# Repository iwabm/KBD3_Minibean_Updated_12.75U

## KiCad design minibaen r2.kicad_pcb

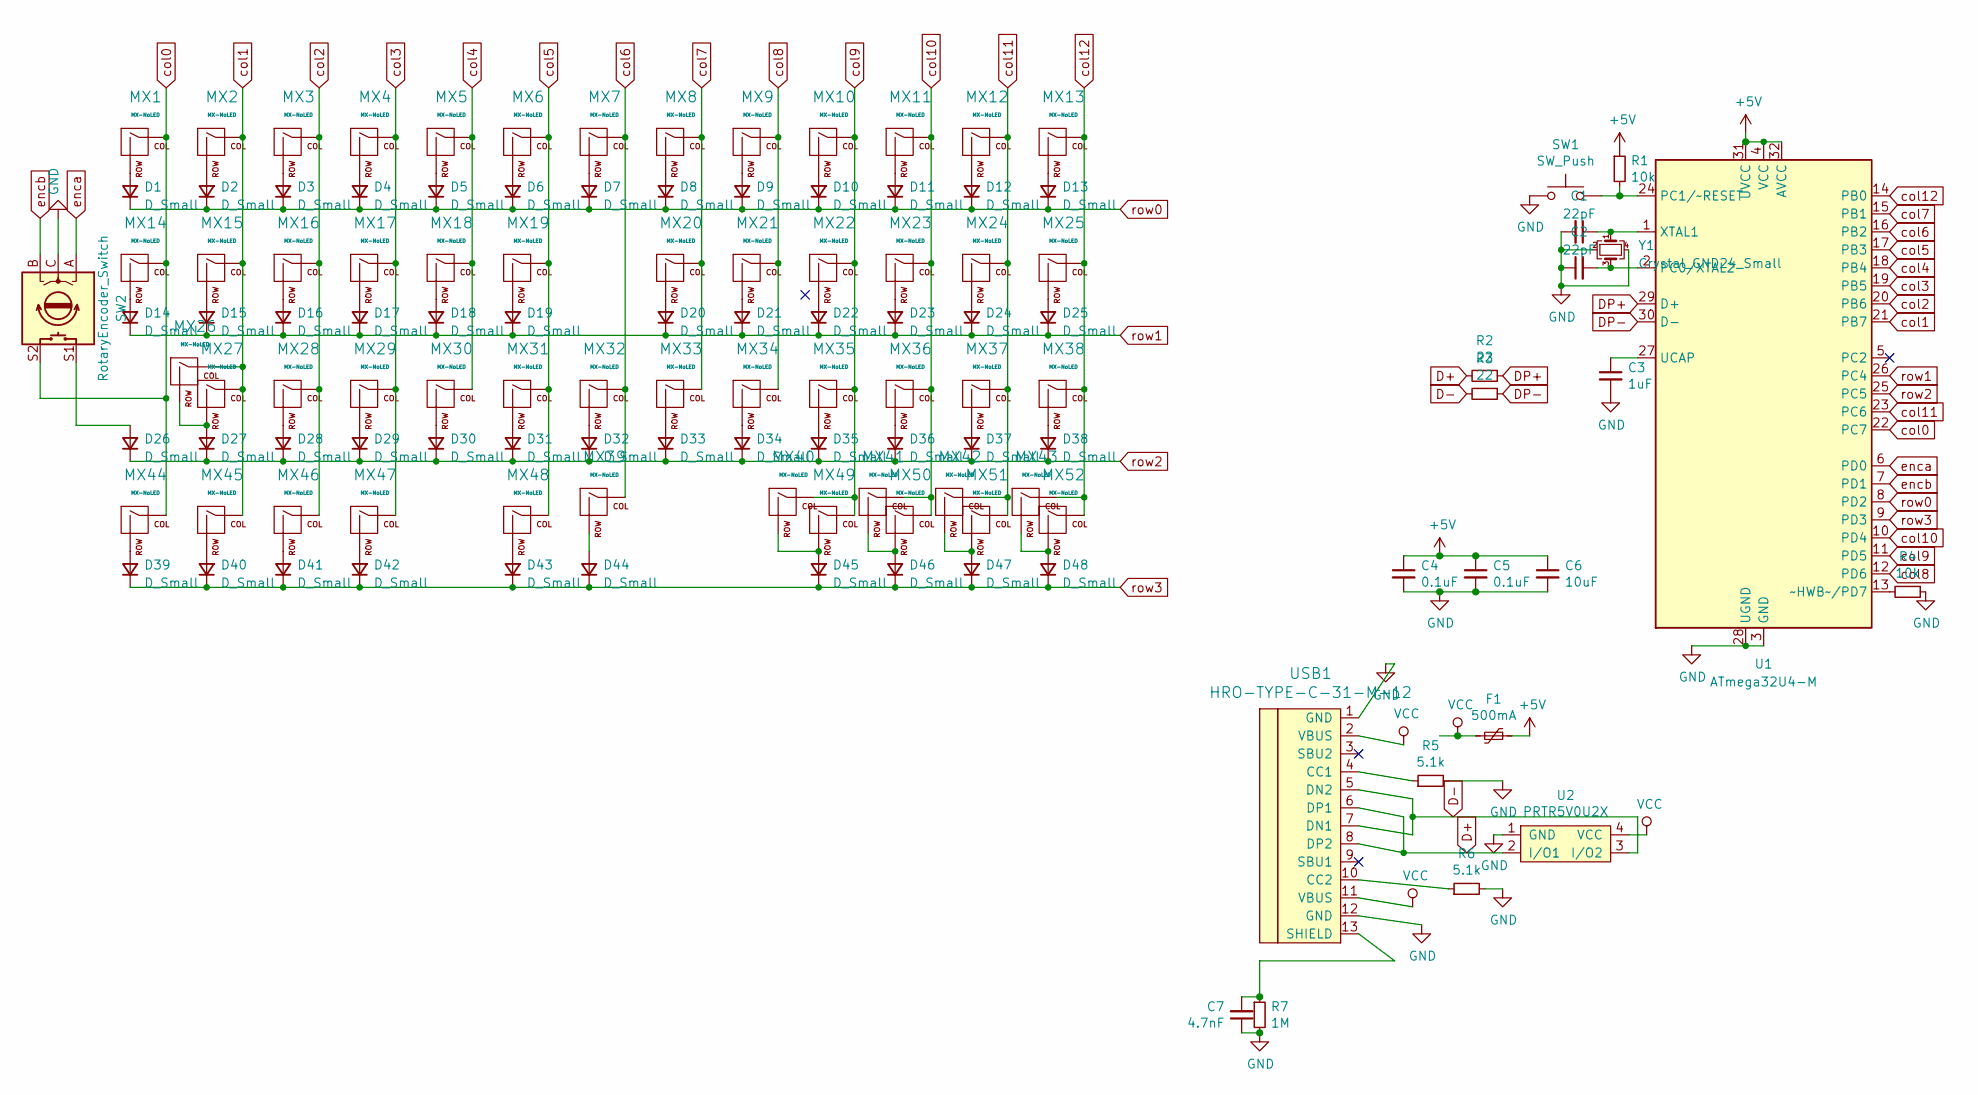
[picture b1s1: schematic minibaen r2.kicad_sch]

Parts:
C1, C2: 22pF; C_0603_1608Metric
C3: 1uF; C_0603_1608Metric
C4, C5: 0.1uF; C_0603_1608Metric
C6: 10uF; C_0603_1608Metric
C7: 4.7nF; C_0603_1608Metric
D1, D2, D3, D4, D5, D6, D7, D8, D9, D10, D11, D12, D13, D14, D15, D16, D17, D18, D19, D20, D21, D22, D23, D24, D25, D26, D27, D28, D29, D30, D31, D32, D33, D34, D35, D36, D37, D38, D39, D40, D41, D42, D43, D44, D45, D46, D47, D48: D_Small; D_SOD-123
F1: 500mA; Fuse_1206_3216Metric
MX1, MX2, MX3, MX4, MX5, MX6, MX7, MX8, MX9, MX10, MX11, MX12, MX13, MX15, MX16, MX17, MX18, MX19, MX20, MX21, MX22, MX23, MX24, MX26, MX28, MX29, MX30, MX31, MX32, MX33, MX34, MX35, MX36, MX37, MX38, MX40, MX41, MX42, MX43, MX45, MX51: MX-NoLED; MXOnly-1U-NoLED
MX14, MX39, MX44, MX46, MX50, MX52: MX-NoLED; MXOnly-1.25U-NoLED
MX25: MX-NoLED; MXOnly-1.5U-NoLED
MX27, MX47, MX49: MX-NoLED; MXOnly-1.75U-NoLED
MX48: MX-NoLED; MXOnly-2.25U-ReversedStabilizers-NoLED
R1, R4: 10k; R_0603_1608Metric
R2, R3: 22; R_0603_1608Metric
R5, R6: 5.1k; R_0603_1608Metric
R7: 1M; R_0603_1608Metric
SW1: SW_Push; SW_Push_SPST_NO_Alps_SKRK
SW2: RotaryEncoder_Switch; RotaryEncoder_EC11-no-legs
U1: ATmega32U4-M; QFN-44-1EP_7x7mm_P0.5mm_EP5.2x5.2mm
U2: PRTR5V0U2X; SOT-143
USB1: HRO-TYPE-C-31-M-12
Y1: Crystal_GND24_Small; Crystal_SMD_3225-4Pin_3.2x2.5mm

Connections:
+5V: C4.1, C5.1, C6.1, F1.1, R1.1, U1.4 (VCC), U1.31 (UVCC), U1.32 (AVCC)
D+: R2.2, U2.2 (I/O1), USB1.6 (DP1), USB1.8 (DP2)
D-: R3.2, U2.3 (I/O2), USB1.5 (DN2), USB1.7 (DN1)
DP+: R2.1, U1.29 (D+)
DP-: R3.1, U1.30 (D-)
GND: C1.2, C2.1, C3.2, C4.2, C5.2, C6.2, C7.1, R4.1, R5.2, R6.2, R7.2, SW1.1, SW2.C, U1.3 (GND), U1.28 (UGND), U2.1 (GND), USB1.1 (GND), USB1.12 (GND), Y1.2, Y1.4
unnamed: C1.1, U1.1 (XTAL1), Y1.1
unnamed: C2.2, U1.2 (PC0/XTAL2), Y1.3
unnamed: C3.1, U1.27 (UCAP)
unnamed: C7.2, R7.1, USB1.13 (SHIELD)
unnamed: D1.2 (A), MX1.2 (ROW)
unnamed: D2.2 (A), MX2.2 (ROW)
unnamed: D3.2 (A), MX3.2 (ROW)
unnamed: D4.2 (A), MX4.2 (ROW)
unnamed: D5.2 (A), MX5.2 (ROW)
unnamed: D6.2 (A), MX6.2 (ROW)
unnamed: D7.2 (A), MX7.2 (ROW)
unnamed: D8.2 (A), MX8.2 (ROW)
unnamed: D9.2 (A), MX9.2 (ROW)
unnamed: D10.2 (A), MX10.2 (ROW)
unnamed: D11.2 (A), MX11.2 (ROW)
unnamed: D12.2 (A), MX12.2 (ROW)
unnamed: D13.2 (A), MX13.2 (ROW)
unnamed: D14.2 (A), MX14.2 (ROW)
unnamed: D15.2 (A), MX15.2 (ROW)
unnamed: D16.2 (A), MX16.2 (ROW)
unnamed: D17.2 (A), MX17.2 (ROW)
unnamed: D18.2 (A), MX18.2 (ROW)
unnamed: D19.2 (A), MX19.2 (ROW)
unnamed: D20.2 (A), MX20.2 (ROW)
unnamed: D21.2 (A), MX21.2 (ROW)
unnamed: D22.2 (A), MX22.2 (ROW)
unnamed: D23.2 (A), MX23.2 (ROW)
unnamed: D24.2 (A), MX24.2 (ROW)
unnamed: D25.2 (A), MX25.2 (ROW)
unnamed: D26.2 (A), SW2.S1
unnamed: D27.2 (A), MX26.2 (ROW), MX27.2 (ROW)
unnamed: D28.2 (A), MX28.2 (ROW)
unnamed: D29.2 (A), MX29.2 (ROW)
unnamed: D30.2 (A), MX30.2 (ROW)
unnamed: D31.2 (A), MX31.2 (ROW)
unnamed: D32.2 (A), MX32.2 (ROW)
unnamed: D33.2 (A), MX33.2 (ROW)
unnamed: D34.2 (A), MX34.2 (ROW)
unnamed: D35.2 (A), MX35.2 (ROW)
unnamed: D36.2 (A), MX36.2 (ROW)
unnamed: D37.2 (A), MX37.2 (ROW)
unnamed: D38.2 (A), MX38.2 (ROW)
unnamed: D39.2 (A), MX44.2 (ROW)
unnamed: D40.2 (A), MX45.2 (ROW)
unnamed: D41.2 (A), MX46.2 (ROW)
unnamed: D42.2 (A), MX47.2 (ROW)
unnamed: D43.2 (A), MX48.2 (ROW)
unnamed: D44.2 (A), MX39.2 (ROW)
unnamed: D45.2 (A), MX40.2 (ROW), MX49.2 (ROW)
unnamed: D46.2 (A), MX41.2 (ROW), MX50.2 (ROW)
unnamed: D47.2 (A), MX42.2 (ROW), MX51.2 (ROW)
unnamed: D48.2 (A), MX43.2 (ROW), MX52.2 (ROW)
unnamed: R1.2, SW1.2, U1.24 (PC1/~RESET)
unnamed: R4.2, U1.13 (~HWB~/PD7)
unnamed: R5.1, USB1.4 (CC1)
unnamed: R6.1, USB1.10 (CC2)
VCC: F1.2, U2.4 (VCC), USB1.2 (VBUS), USB1.11 (VBUS)
col0: MX1.1 (COL), MX14.1 (COL), MX44.1 (COL), SW2.S2, U1.22 (PC7)
col1: MX2.1 (COL), MX15.1 (COL), MX26.1 (COL), MX27.1 (COL), MX45.1 (COL), U1.21 (PB7)
col2: MX3.1 (COL), MX16.1 (COL), MX28.1 (COL), MX46.1 (COL), U1.20 (PB6)
col3: MX4.1 (COL), MX17.1 (COL), MX29.1 (COL), MX47.1 (COL), U1.19 (PB5)
col4: MX5.1 (COL), MX18.1 (COL), MX30.1 (COL), U1.18 (PB4)
col5: MX6.1 (COL), MX19.1 (COL), MX31.1 (COL), MX48.1 (COL), U1.17 (PB3)
col6: MX7.1 (COL), MX32.1 (COL), MX39.1 (COL), U1.16 (PB2)
col7: MX8.1 (COL), MX20.1 (COL), MX33.1 (COL), U1.15 (PB1)
col8: MX9.1 (COL), MX21.1 (COL), MX34.1 (COL), U1.12 (PD6)
col9: MX10.1 (COL), MX22.1 (COL), MX35.1 (COL), MX40.1 (COL), MX49.1 (COL), U1.11 (PD5)
col10: MX11.1 (COL), MX23.1 (COL), MX36.1 (COL), MX41.1 (COL), MX50.1 (COL), U1.10 (PD4)
col11: MX12.1 (COL), MX24.1 (COL), MX37.1 (COL), MX42.1 (COL), MX51.1 (COL), U1.23 (PC6)
col12: MX13.1 (COL), MX25.1 (COL), MX38.1 (COL), MX43.1 (COL), MX52.1 (COL), U1.14 (PB0)
enca: SW2.A, U1.6 (PD0)
encb: SW2.B, U1.7 (PD1)
row0: D1.1 (K), D2.1 (K), D3.1 (K), D4.1 (K), D5.1 (K), D6.1 (K), D7.1 (K), D8.1 (K), D9.1 (K), D10.1 (K), D11.1 (K), D12.1 (K), D13.1 (K), U1.8 (PD2)
row1: D14.1 (K), D15.1 (K), D16.1 (K), D17.1 (K), D18.1 (K), D19.1 (K), D20.1 (K), D21.1 (K), D22.1 (K), D23.1 (K), D24.1 (K), D25.1 (K), U1.26 (PC4)
row2: D26.1 (K), D27.1 (K), D28.1 (K), D29.1 (K), D30.1 (K), D31.1 (K), D32.1 (K), D33.1 (K), D34.1 (K), D35.1 (K), D36.1 (K), D37.1 (K), D38.1 (K), U1.25 (PC5)
row3: D39.1 (K), D40.1 (K), D41.1 (K), D42.1 (K), D43.1 (K), D44.1 (K), D45.1 (K), D46.1 (K), D47.1 (K), D48.1 (K), U1.9 (PD3)

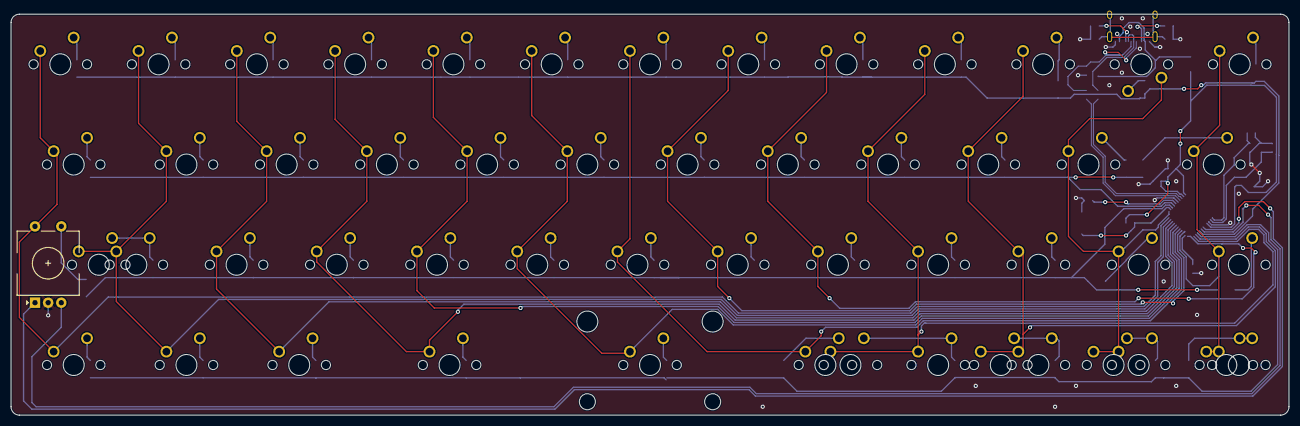
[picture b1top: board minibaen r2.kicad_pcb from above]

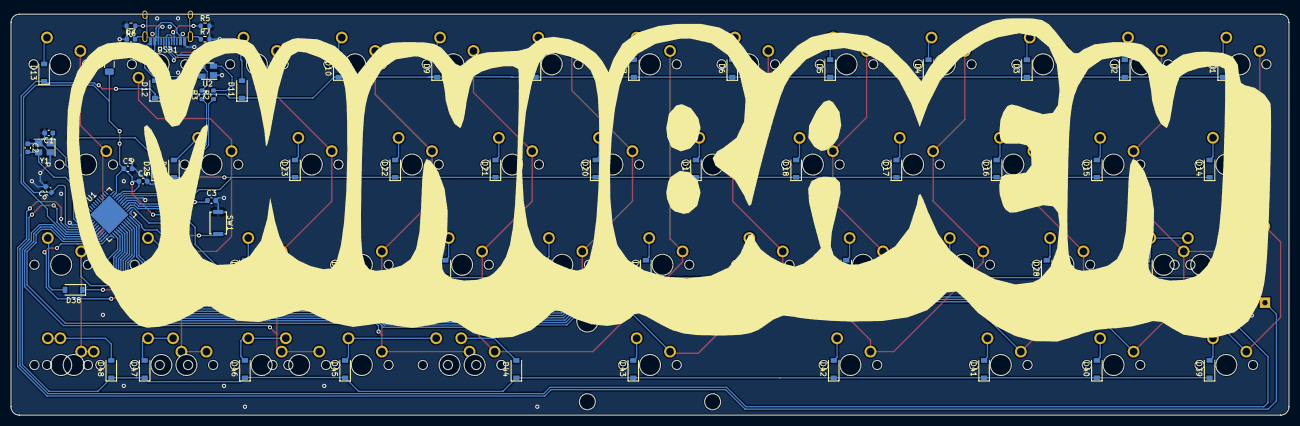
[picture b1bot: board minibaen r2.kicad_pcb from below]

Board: 2 copper layers, 242.9 x 76.2 mm, 121 parts (68 on the bottom side), 82 nets.

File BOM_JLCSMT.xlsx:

Comment | Designator | Footprint | JLCPCB Part #（optional）
Diode_SMD | D1-D48 | Diode_SMD:D_SOD-123 | C64898
22pF | C1, C2 | Capacitor_SMD:C_0603_1608Metric | C1653
1uF | C3 | Capacitor_SMD:C_0603_1608Metric | C15849
0.1uF | C4, C5 | Capacitor_SMD:C_0603_1608Metric | C14663
10uF | C6 | Capacitor_SMD:C_0603_1608Metric | C19702
4.7nF | C7 | Capacitor_SMD:C_0603_1608Metric | C53987
10k | R1, R4 | Resistor_SMD:R_0603_1608Metric | C25804
22 | R2, R3 | Resistor_SMD:R_0603_1608Metric | C23345
5.1k | R5, R6 | Resistor_SMD:R_0603_1608Metric | C23186
1M | R7 | Resistor_SMD:R_0603_1608Metric | C22935
Fuse | F1 | Fuse:Fuse_1206_3216Metric | C70076
Switch | SW1 | Button_Switch_SMD:SW_Push_SPST_NO_Alps_SKRK | C561519
PRTR5V0U2X | U2 | Package_TO_SOT_SMD:SOT-23-6 | C384891
ATmega32U4-M | U1 | Package_DFN_QFN:QFN-44-1EP_7x7mm_P0.5mm_EP5.2x5.2mm | C112161
USB | USB1 | Type-C:HRO-TYPE-C-31-M-12-Assembly | C165948
Crystal | Y1 | Crystal:Crystal_SMD_3225-4Pin_3.2x2.5mm | C13738

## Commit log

2023-09-27 Add submodules
